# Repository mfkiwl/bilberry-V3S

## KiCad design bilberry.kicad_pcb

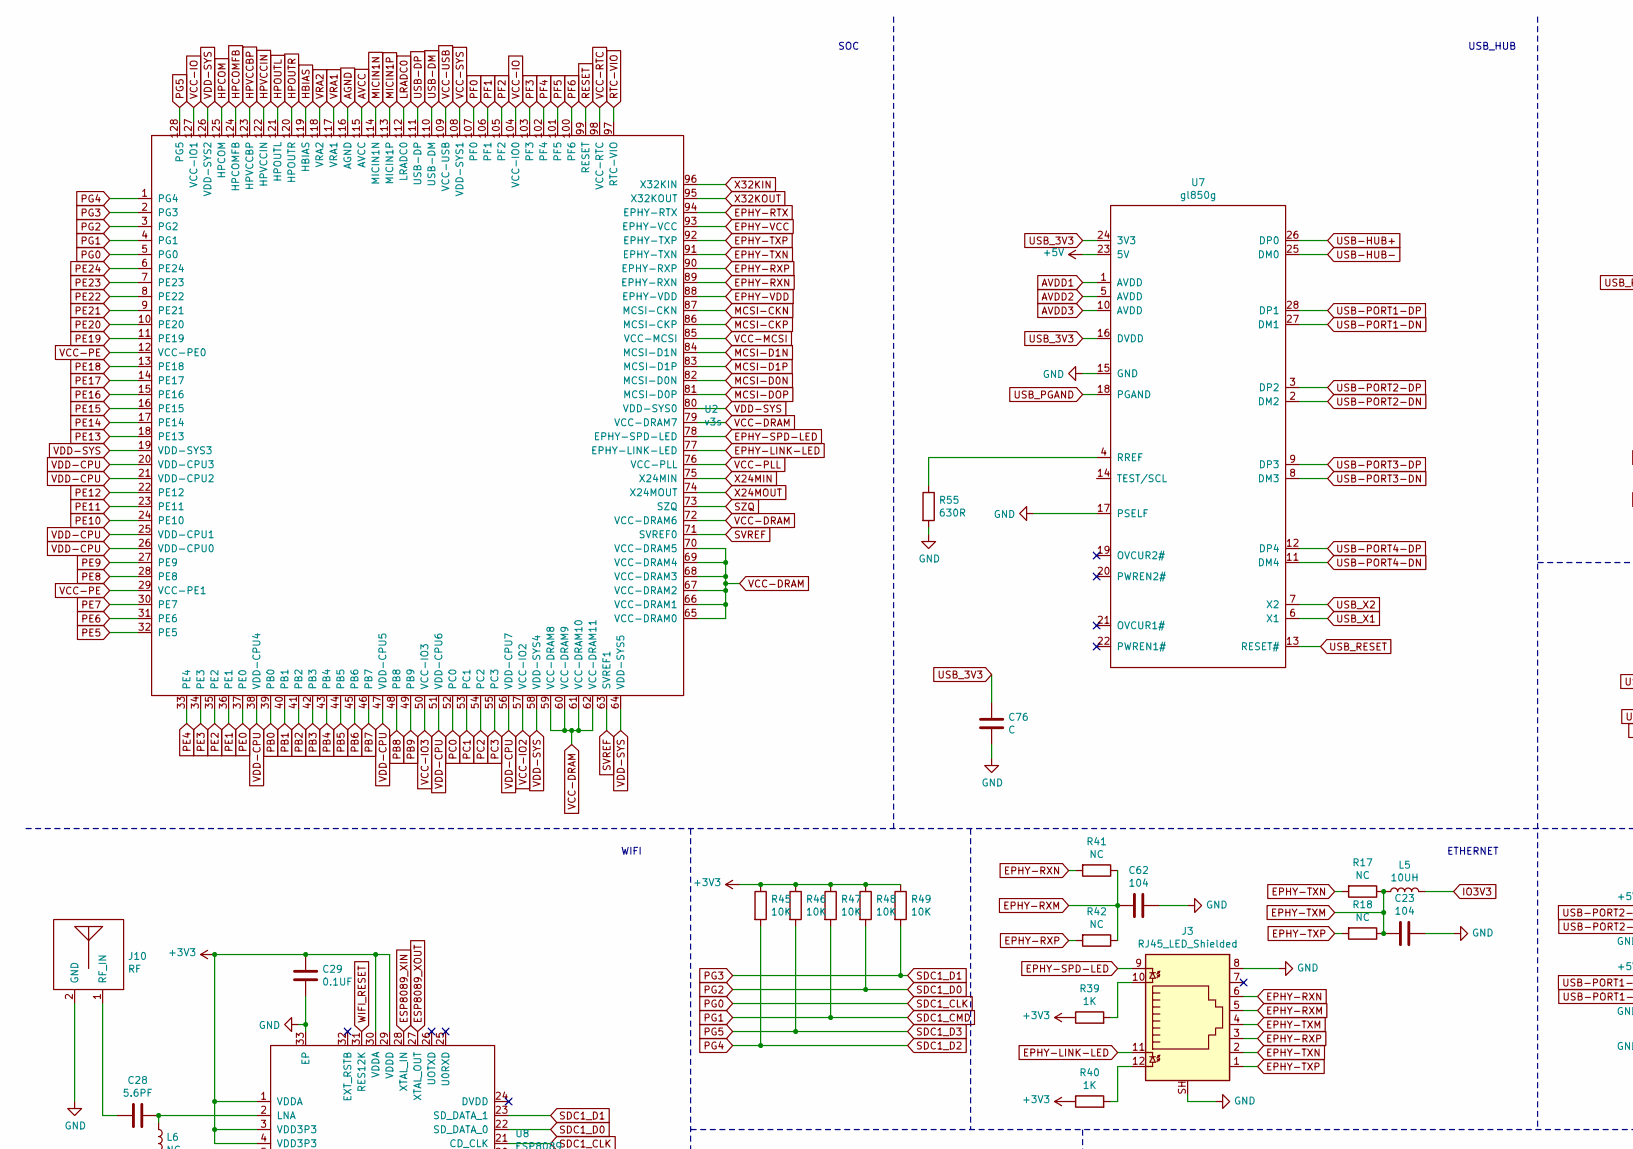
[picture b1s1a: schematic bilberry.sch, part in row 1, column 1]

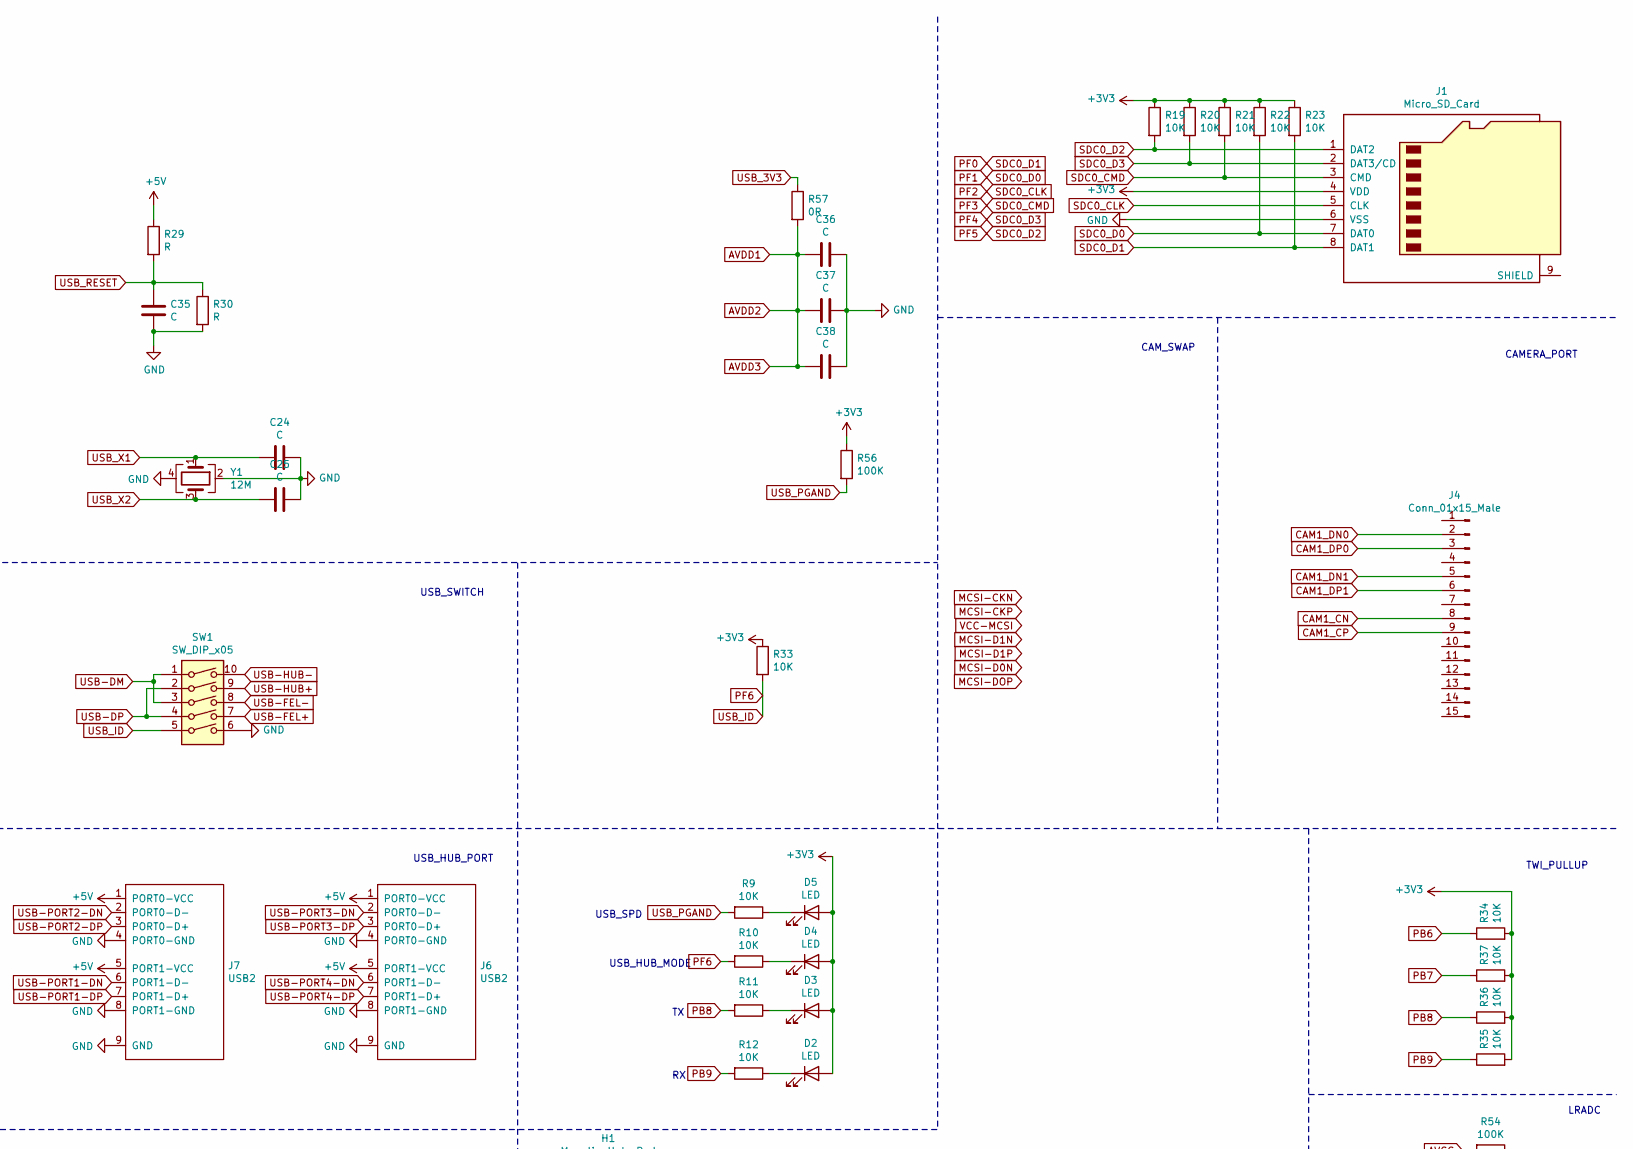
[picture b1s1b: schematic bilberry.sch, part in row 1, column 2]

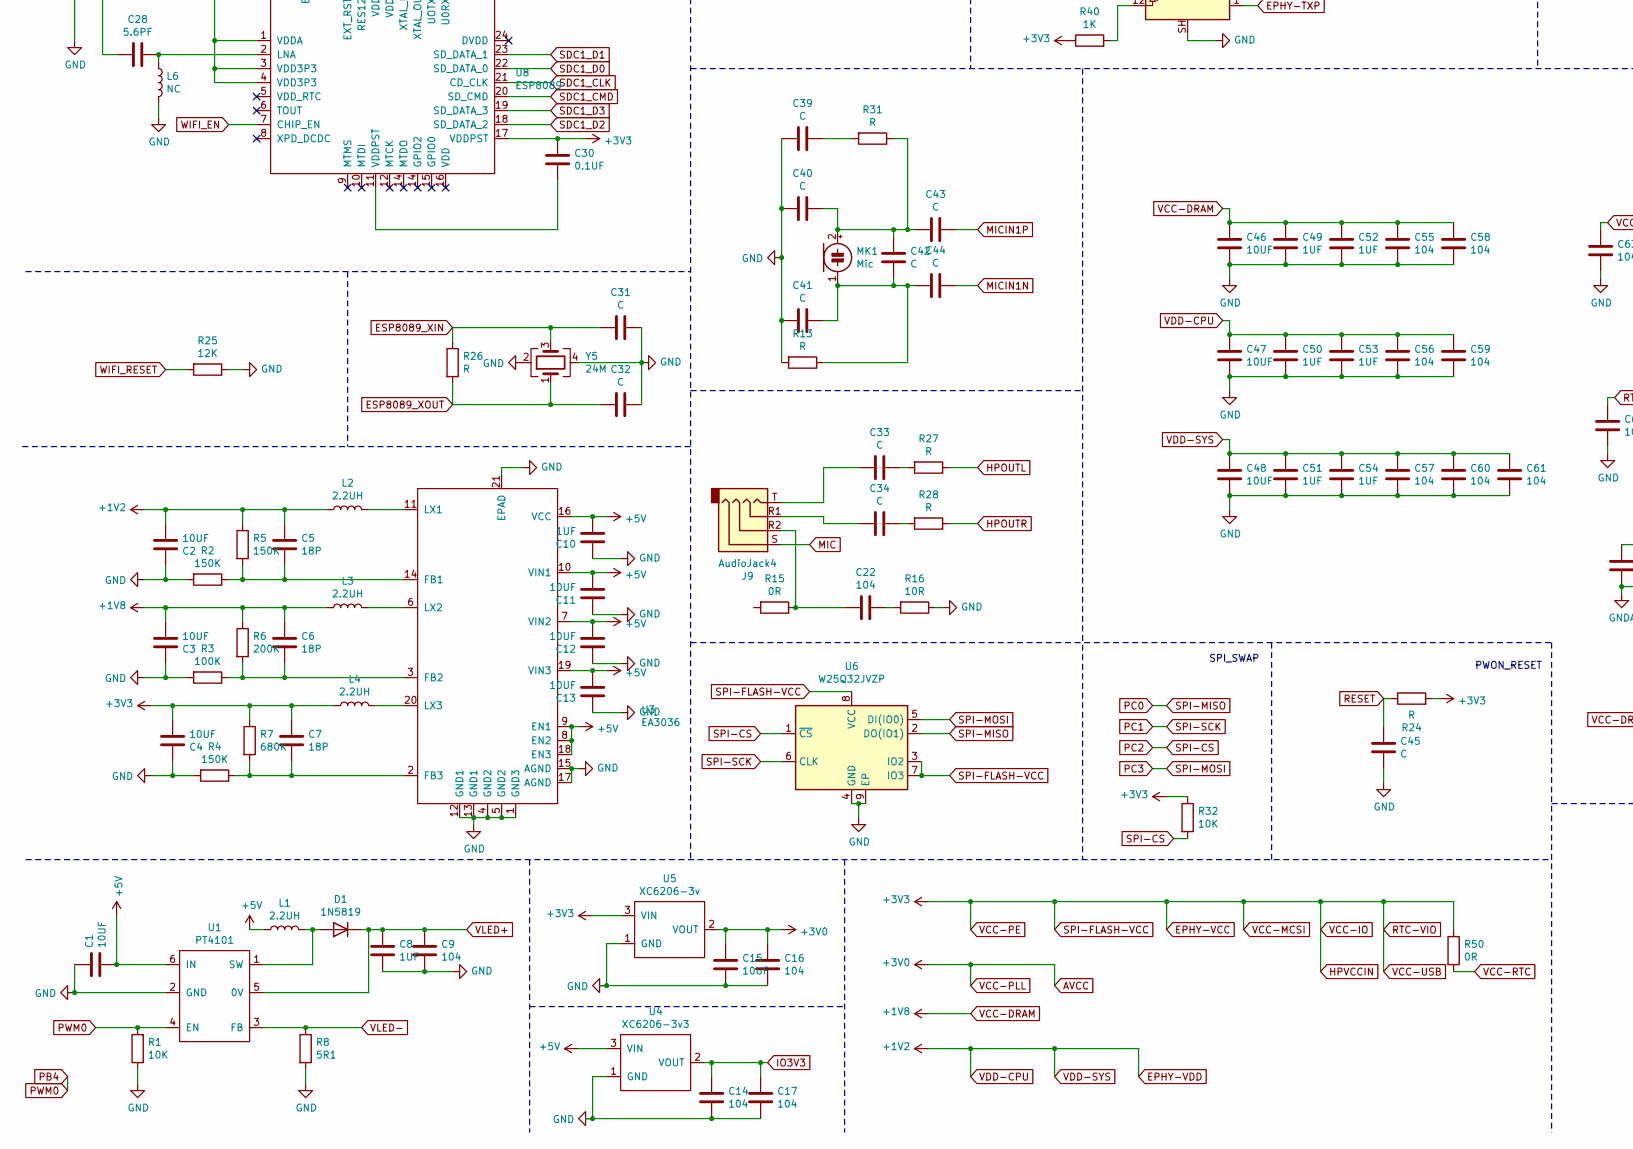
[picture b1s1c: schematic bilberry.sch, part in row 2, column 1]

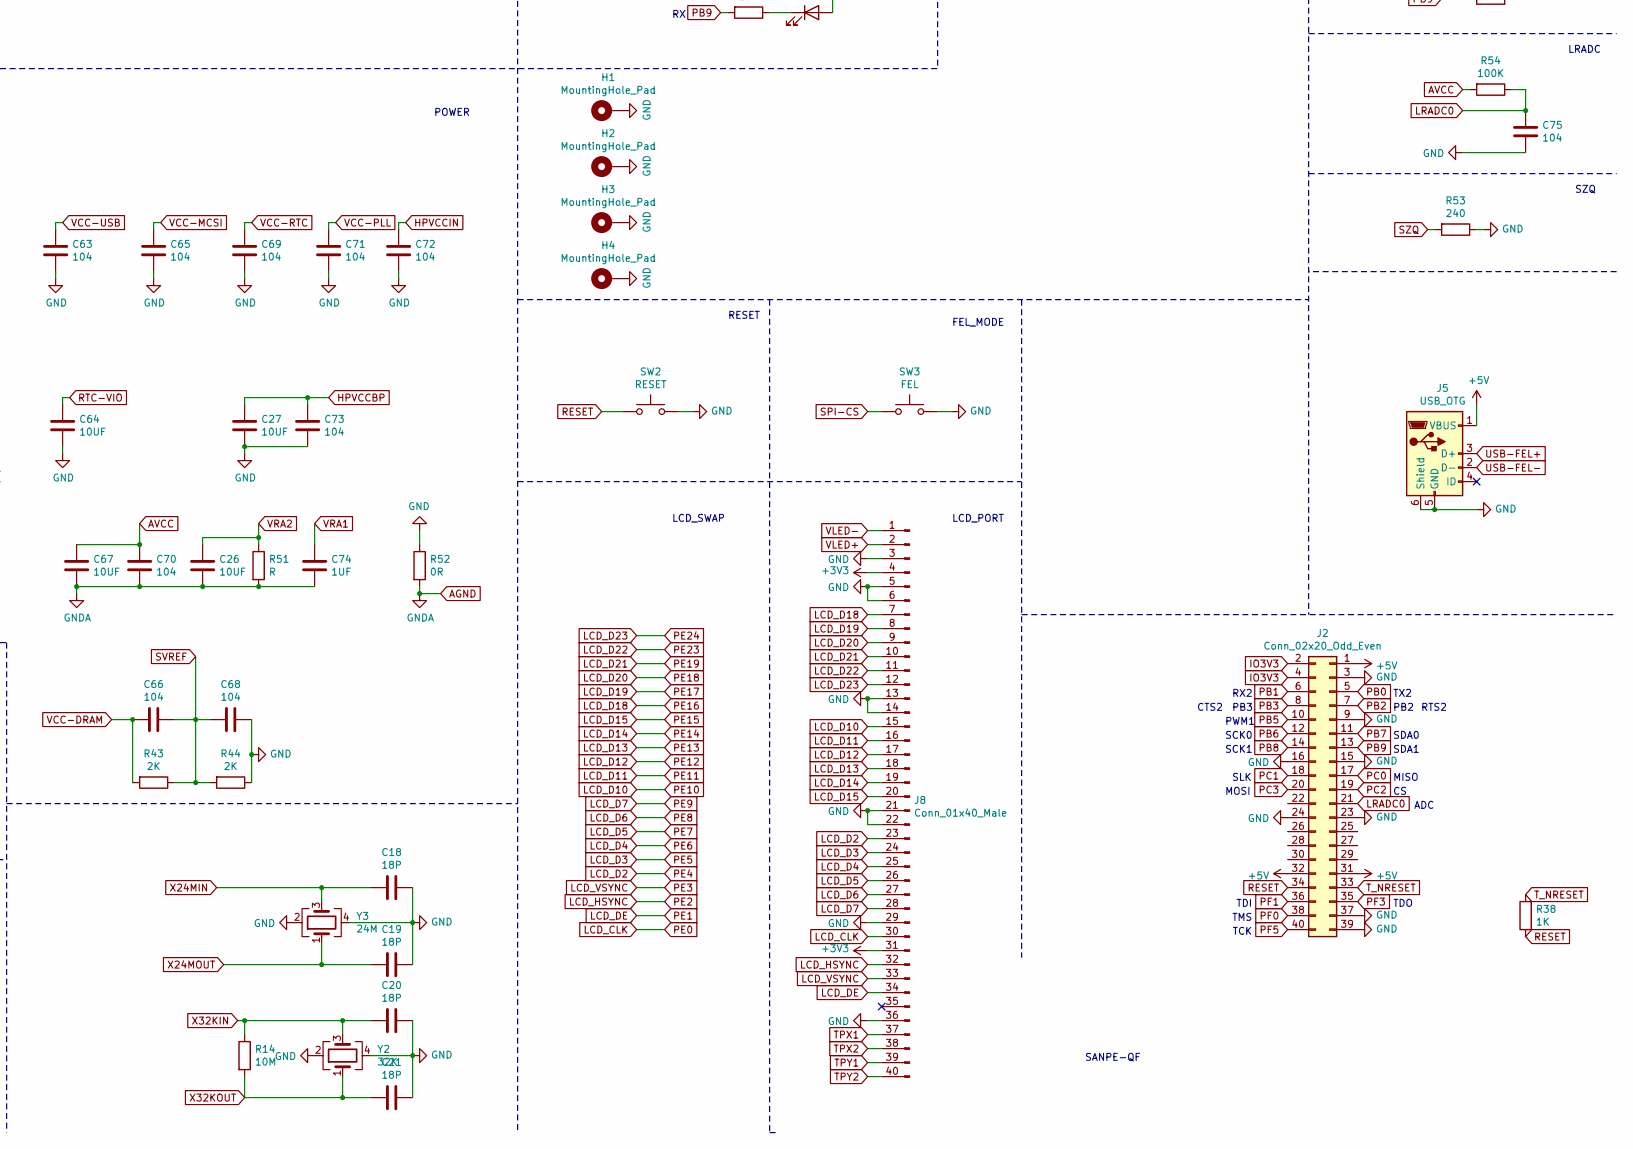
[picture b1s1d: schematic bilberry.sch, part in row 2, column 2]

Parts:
C1, C15, C26, C27, C46, C47, C48, C64, C67: 10UF; C_0603_1608Metric
C2, C3, C4, C11, C12, C13: 10UF; C_0805_2012Metric
C5, C6, C7, C18, C19, C20, C21: 18P; C_0603_1608Metric
C8, C49, C50, C51, C52, C53, C54, C74: 1UF; C_0603_1608Metric
C9, C14, C16, C17, C22, C23, C55, C56, C57, C58, C59, C60, C61, C62, C63, C65, C66, C68, C69, C70, C71, C72, C73, C75: 104; C_0603_1608Metric
C10: 1UF; C_0805_2012Metric
C24, C25, C31, C32, C33, C34, C35, C36, C37, C38, C39, C40, C41, C42, C43, C44, C45, C76: C; C_0603_1608Metric
C28: 5.6PF; C_0603_1608Metric
C29, C30: 0.1UF; C_0603_1608Metric
D1: 1N5819; D_0603_1608Metric
D2, D3, D4, D5: LED; LED_0603_1608Metric
H1, H2, H3, H4: MountingHole_Pad; MountingHole_2.7mm_Pad_Via
J1: Micro_SD_Card; microSD_HC_Molex_104031-0811
J2: Conn_02x20_Odd_Even; PinHeader_2x20_P2.54mm_Vertical
J3: RJ45_LED_Shielded; RJ45_Hanrun_HR911105A
J4: Conn_01x15_Male; Molex_200528-0150_1x15-1MP_P1.00mm_Horizontal
J5: USB_OTG; USB_Micro-B_Molex-105017-0001
J6, J7: USB2
J8: Conn_01x40_Male; Hirose_FH12-40S-0.5SH_1x40-1MP_P0.50mm_Horizontal
J9: AudioJack4; Jack_3.5mm_PJ320D_Horizontal
J10: RF
L1, L2, L3, L4: 2.2UH; L_Coilcraft_XAL5030
L5: 10UH; L_0603_1608Metric
L6: NC; L_0603_1608Metric
MK1: Mic
R1, R9, R10, R11, R12, R19, R20, R21, R22, R23, R32, R33, R34, R35, R36, R37, R45, R46, R47, R48, R49: 10K; R_0603_1608Metric
R2, R4, R5: 150K; R_0603_1608Metric
R3, R54, R56: 100K; R_0603_1608Metric
R6: 200K; R_0603_1608Metric
R7: 680K; R_0603_1608Metric
R8: 5R1; R_0603_1608Metric
R13, R24, R26, R27, R28, R29, R30, R31, R51: R; R_0603_1608Metric
R14: 10M; R_0603_1608Metric
R15, R50, R52, R57: 0R; R_0603_1608Metric
R16: 10R; R_0603_1608Metric
R17, R18, R41, R42: NC; R_0603_1608Metric
R25: 12K; R_0603_1608Metric
R38, R39, R40: 1K; R_0603_1608Metric
R43, R44: 2K; R_0603_1608Metric
R53: 240; R_0603_1608Metric
R55: 630R; R_0603_1608Metric
SW1: SW_DIP_x05; SW_DIP_SPSTx05_Slide_9.78x14.88mm_W7.62mm_P2.54mm
SW2: RESET; SW_SPST_B3U-1000P
SW3: FEL; SW_SPST_B3U-1000P
U1: PT4101; TSOT-23-6
U2: v3s; TQFP-128_14x14mm_P0.4mm
U3: EA3036; QFN-20-1EP_5x5mm_P0.65mm_EP3.35x3.35mm_ThermalVias
U4: XC6206-3v3; Potentiometer_Bourns_3224W_Vertical
U5: XC6206-3v; Potentiometer_Bourns_3224W_Vertical
U6: W25Q32JVZP; WSON-8-1EP_6x5mm_P1.27mm_EP3.4x4.3mm
U7: gl850g; SSOP-28_5.3x10.2mm_P0.65mm
U8: ESP8089; QFN-32-1EP_5x5mm_P0.5mm_EP3.6x3.6mm_ThermalVias
Y1: 12M; Crystal_SMD_3225-4Pin_3.2x2.5mm
Y2: 32K; Crystal_SMD_3225-4Pin_3.2x2.5mm
Y3, Y5: 24M; Crystal_SMD_3225-4Pin_3.2x2.5mm

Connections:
+5V: C1.2, C10.2, C11.2, C12.2, C13.2, J2.1, J2.31, J2.32, J5.1 (VBUS), J6.1 (PORT0-VCC), J6.5 (PORT1-VCC), J7.1 (PORT0-VCC), J7.5 (PORT1-VCC), L1.1, R29.1, U1.6 (IN), U3.7 (VIN2), U3.8 (EN2), U3.9 (EN1), U3.10 (VIN1), U3.16 (VCC), U3.18 (EN3), U3.19 (VIN3), U4.3 (VIN), U7.23 (5V)
AGND: C26.2, C67.2, C70.2, C74.2, R51.2, R52.2, U2.116 (AGND)
AVCC: C15.1, C16.1, C67.1, C70.1, C71.1, R54.2, U2.76 (VCC-PLL), U2.115 (AVCC), U5.2 (VOUT)
AVDD1: C36.2, C37.2, C38.2, R57.2, U7.1 (AVDD), U7.5 (AVDD), U7.10 (AVDD)
CAM1_CN: J4.8
CAM1_CP: J4.9
CAM1_DN0: J4.2
CAM1_DN1: J4.5
CAM1_DP0: J4.3
CAM1_DP1: J4.6
EPHY-LINK-LED: J3.11, U2.77 (EPHY-LINK-LED)
EPHY-RTX: U2.94 (EPHY-RTX)
EPHY-RXM: C62.2, J3.5, R41.1, R42.1
EPHY-RXN: J3.6, R41.2, U2.89 (EPHY-RXN)
EPHY-RXP: J3.3, R42.2, U2.90 (EPHY-RXP)
EPHY-SPD-LED: J3.9, U2.78 (EPHY-SPD-LED)
EPHY-TXM: C23.2, J3.4, L5.1, R17.1, R18.1
EPHY-TXN: J3.2, R17.2, U2.91 (EPHY-TXN)
EPHY-TXP: J3.1, R18.2, U2.92 (EPHY-TXP)
EPHY-VCC: C4.2, C7.1, C29.1, C30.1, C63.1, C64.1, C65.1, C72.1, D2.2 (A), D3.2 (A), D4.2 (A), D5.2 (A), J1.4 (VDD), J8.4, J8.31, L4.1, R7.1, R19.1, R20.1, R21.1, R22.1, R23.1, R24.2, R32.1, R33.1, R34.2, R35.2, R36.2, R37.2, R39.1, R40.1, R45.1, R46.1, R47.1, R48.1, R49.1, R50.1, R56.1, U2.12 (VCC-PE0), U2.29 (VCC-PE1), U2.85 (VCC-MCSI), U2.93 (EPHY-VCC), U2.97 (RTC-VIO), U2.104 (VCC-IO0), U2.109 (VCC-USB), U2.122 (HPVCCIN), U2.127 (VCC-IO1), U5.3 (VIN), U6.3 (IO2), U6.7 (IO3), U6.8 (VCC), U8.1 (VDDA), U8.3 (VDD3P3), U8.4 (VDD3P3), U8.17 (VDDPST), U8.29 (VDDD), U8.30 (VDDA)
EPHY-VDD: C2.2, C5.1, C47.1, C48.1, C50.1, C51.1, C53.1, C54.1, C56.1, C57.1, C59.1, C60.1, C61.1, L2.1, R5.1, U2.19 (VDD-SYS3), U2.20 (VDD-CPU3), U2.21 (VDD-CPU2), U2.25 (VDD-CPU1), U2.26 (VDD-CPU0), U2.38 (VDD-CPU4), U2.47 (VDD-CPU5), U2.51 (VDD-CPU6), U2.56 (VDD-CPU7), U2.58 (VDD-SYS4), U2.64 (VDD-SYS5), U2.80 (VDD-SYS0), U2.88 (EPHY-VDD), U2.126 (VDD-SYS2)
ESP8089_XIN: C31.1, R26.1, U8.28 (XTAL_IN), Y5.3
ESP8089_XOUT: C32.1, R26.2, U8.27 (XTAL_OUT), Y5.1
GND: C1.1, C2.1, C3.1, C4.1, C8.2, C9.2, C10.1, C11.1, C12.1, C13.1, C14.2, C15.2, C16.2, C17.2, C18.2, C19.2, C20.2, C21.2, C23.1, C24.1, C25.1, C27.2, C29.2, C31.2, C32.2, C35.2, C36.1, C37.1, C38.1, C39.2, C40.2, C41.2, C45.2, C46.2, C47.2, C48.2, C49.2, C50.2, C51.2, C52.2, C53.2, C54.2, C55.2, C56.2, C57.2, C58.2, C59.2, C60.2, C61.2, C62.1, C63.2, C64.2, C65.2, C68.1, C69.2, C71.2, C72.2, C73.2, C75.2, C76.2, H1.1, H2.1, H3.1, H4.1, J1.6 (VSS), J2.3, J2.9, J2.15, J2.16, J2.23, J2.24, J2.37, J2.39, J3.8, J3.SH, J5.5 (GND), J5.6 (Shield), J6.4 (PORT0-GND), J6.8 (PORT1-GND), J6.9 (GND), J7.4 (PORT0-GND), J7.8 (PORT1-GND), J7.9 (GND), J8.3, J8.5, J8.6, J8.13, J8.14, J8.21, J8.22, J8.29, J8.36, J10.2 (GND), L6.2, R1.1, R2.2, R3.2, R4.2, R8.2, R13.2, R16.1, R25.1, R30.2, R44.1, R52.1, R53.1, R55.2, SW1.6, SW2.2, SW3.2, U1.2 (GND), U3.1 (GND3), U3.4 (GND2), U3.5 (GND2), U3.12 (GND1), U3.13 (GND1), U3.15 (AGND), U3.17 (AGND), U3.21 (EPAD), U4.1 (GND), U5.1 (GND), U6.4 (GND), U6.9 (EP), U7.15 (GND), U7.17 (PSELF), U8.33 (EP), Y1.2, Y1.4, Y2.2, Y2.4, Y3.2, Y3.4, Y5.2, Y5.4
HBIAS: U2.119 (HBIAS)
HPCOM: U2.125 (HPCOM)
HPCOMFB: U2.124 (HPCOMFB)
HPOUTL: R27.1, U2.121 (HPOUTL)
HPOUTR: R28.1, U2.120 (HPOUTR)
HPVCCBP: C27.1, C73.1, U2.123 (HPVCCBP)
IO3V3: C14.1, C17.1, J2.2, J2.4, L5.2, U4.2 (VOUT)
LCD_CLK: J8.30, U2.37 (PE0)
LCD_D2: J8.23, U2.33 (PE4)
LCD_D3: J8.24, U2.32 (PE5)
LCD_D4: J8.25, U2.31 (PE6)
LCD_D5: J8.26, U2.30 (PE7)
LCD_D6: J8.27, U2.28 (PE8)
LCD_D7: J8.28, U2.27 (PE9)
LCD_D10: J8.15, U2.24 (PE10)
LCD_D11: J8.16, U2.23 (PE11)
LCD_D12: J8.17, U2.22 (PE12)
LCD_D13: J8.18, U2.18 (PE13)
LCD_D14: J8.19, U2.17 (PE14)
LCD_D15: J8.20, U2.16 (PE15)
LCD_D18: J8.7, U2.15 (PE16)
LCD_D19: J8.8, U2.14 (PE17)
LCD_D20: J8.9, U2.13 (PE18)
LCD_D21: J8.10, U2.11 (PE19)
LCD_D22: J8.11, U2.7 (PE23)
LCD_D23: J8.12, U2.6 (PE24)
LCD_DE: J8.34, U2.36 (PE1)
LCD_HSYNC: J8.32, U2.35 (PE2)
LCD_VSYNC: J8.33, U2.34 (PE3)
LRADC0: C75.1, J2.21, R54.1, U2.112 (LRADC0)
MCSI-CKN: U2.87 (MCSI-CKN)
MCSI-CKP: U2.86 (MCSI-CKP)
MCSI-D0N: U2.82 (MCSI-D0N)
MCSI-D1N: U2.84 (MCSI-D1N)
MCSI-D1P: U2.83 (MCSI-D1P)
MCSI-DOP: U2.81 (MCSI-D0P)
MIC: J9.S
MICIN1N: C44.2, U2.114 (MICIN1N)
MICIN1P: C43.2, U2.113 (MICIN1P)
unnamed: C5.2, R2.1, R5.2, U3.14 (FB1)
unnamed: C6.2, R3.1, R6.2, U3.3 (FB2)
unnamed: C7.2, R4.1, R7.2, U3.2 (FB3)
unnamed: C22.1, R16.2
unnamed: C22.2, J9.R2, R15.1
unnamed: C28.1, L6.1, U8.2 (LNA)
unnamed: C28.2, J10.1 (RF_IN)
unnamed: C30.2, U8.11 (VDDPST)
unnamed: C33.1, J9.T
unnamed: C33.2, R27.2
unnamed: C34.1, J9.R1
unnamed: C34.2, R28.2
unnamed: C39.1, R31.2
unnamed: C40.1, C42.1, C43.1, MK1.2 (+), R31.1
unnamed: C41.1, C42.2, C44.1, MK1.1 (-), R13.1
unnamed: D1.2 (A), L1.2, U1.1 (SW)
unnamed: D2.1 (K), R12.1
unnamed: D3.1 (K), R11.1
unnamed: D4.1 (K), R10.1
unnamed: D5.1 (K), R9.1
unnamed: J3.10, R39.2
unnamed: J3.12, R40.2
unnamed: L2.2, U3.11 (LX1)
unnamed: L3.2, U3.6 (LX2)
unnamed: L4.2, U3.20 (LX3)
unnamed: R55.1, U7.4 (RREF)
PB0: J2.5, U2.39 (PB0)
PB1: J2.6, U2.40 (PB1)
PB2: J2.7, U2.41 (PB2)
PB3: J2.8, U2.42 (PB3)
PB4: R1.2, U1.4 (EN), U2.43 (PB4)
PB5: J2.10, U2.44 (PB5)
PB6: J2.12, R34.1, U2.45 (PB6)
PB7: J2.11, R37.1, U2.46 (PB7)
PB8: J2.14, R11.2, R36.1, U2.48 (PB8)
PB9: J2.13, R12.2, R35.1, U2.49 (PB9)
PC0: J2.17, U2.52 (PC0), U6.2 (DO(IO1))
PC1: J2.18, U2.53 (PC1), U6.6 (CLK)
PC2: J2.19, R32.2, SW3.1, U2.54 (PC2), U6.1 (~CS)
PC3: J2.20, U2.55 (PC3), U6.5 (DI(IO0))
PE20: U2.10 (PE20)
PE21: U2.9 (PE21)
PE22: U2.8 (PE22)
PF6: R10.2, R33.2, SW1.5, U2.100 (PF6)
PG0: U2.5 (PG0), U8.21 (CD_CLK)
PG1: R47.2, U2.4 (PG1), U8.20 (SD_CMD)
PG2: R48.2, U2.3 (PG2), U8.22 (SD_DATA_0)
PG3: R49.2, U2.2 (PG3), U8.23 (SD_DATA_1)
PG4: R45.2, U2.1 (PG4), U8.18 (SD_DATA_2)
PG5: R46.2, U2.128 (PG5), U8.19 (SD_DATA_3)
RESET: C45.1, J2.34, R24.1, R38.1, SW2.1, U2.99 (RESET)
SVREF: C66.1, C68.2, R43.1, R44.2, U2.63 (SVREF1), U2.71 (SVREF0)
SZQ: R53.2, U2.73 (SZQ)
TPX1: J8.37
TPX2: J8.38
TPY1: J8.39
TPY2: J8.40
T_NRESET: J2.33, R38.2
USB-DM: SW1.1, SW1.3, U2.110 (USB-DM)
USB-DP: SW1.2, SW1.4, U2.111 (USB-DP)
USB-FEL+: J5.3 (D+), SW1.7
USB-FEL-: J5.2 (D-), SW1.8
USB-HUB+: SW1.9, U7.26 (DP0)
USB-HUB-: SW1.10, U7.25 (DM0)
USB-PORT1-DN: J7.6 (PORT1-D-), U7.27 (DM1)
USB-PORT1-DP: J7.7 (PORT1-D+), U7.28 (DP1)
USB-PORT2-DN: J7.2 (PORT0-D-), U7.2 (DM2)
USB-PORT2-DP: J7.3 (PORT0-D+), U7.3 (DP2)
USB-PORT3-DN: J6.2 (PORT0-D-), U7.8 (DM3)
USB-PORT3-DP: J6.3 (PORT0-D+), U7.9 (DP3)
USB-PORT4-DN: J6.6 (PORT1-D-), U7.11 (DM4)
USB-PORT4-DP: J6.7 (PORT1-D+), U7.12 (DP4)
USB_3V3: C76.1, R57.1, U7.16 (DVDD), U7.24 (3V3)
USB_PGAND: R9.2, R56.2, U7.18 (PGAND)
USB_RESET: C35.1, R29.2, R30.1, U7.13 (RESET#)
USB_X1: C24.2, U7.6 (X1), Y1.1
USB_X2: C25.2, U7.7 (X2), Y1.3
VCC-DRAM: C3.2, C6.1, C46.1, C49.1, C52.1, C55.1, C58.1, C66.2, L3.1, R6.1, R43.2, U2.59 (VCC-DRAM8), U2.60 (VCC-DRAM9), U2.61 (VCC-DRAM10), U2.62 (VCC-DRAM11), U2.65 (VCC-DRAM0), U2.66 (VCC-DRAM1), U2.67 (VCC-DRAM2), U2.68 (VCC-DRAM3), U2.69 (VCC-DRAM4), U2.70 (VCC-DRAM5), U2.72 (VCC-DRAM6), U2.79 (VCC-DRAM7)
VCC-IO2: U2.57 (VCC-IO2)
VCC-IO3: U2.50 (VCC-IO3)
VCC-RTC: C69.1, R50.2, U2.98 (VCC-RTC)
VCC-SYS: U2.108 (VDD-SYS1)
VLED+: C8.1, C9.1, D1.1 (K), J8.2, U1.5 (0V)
VLED-: J8.1, R8.1, U1.3 (FB)
VRA1: C74.1, U2.117 (VRA1)
VRA2: C26.1, R51.1, U2.118 (VRA2)
WIFI_EN: U8.7 (CHIP_EN)
WIFI_RESET: R25.2, U8.31 (RES12K)
X24MIN: C18.1, U2.75 (X24MIN), Y3.3
X24MOUT: C19.1, U2.74 (X24MOUT), Y3.1
X32KIN: C20.1, R14.1, U2.96 (X32KIN), Y2.3
X32KOUT: C21.1, R14.2, U2.95 (X32KOUT), Y2.1

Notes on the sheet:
SANPE-QF
TX2
RX2
PB2
PB3
PWM1
SCK0
SDA0
SCK1
SDA1
MISO
SLK
MOSI
ADC
TDI
TMS
TCK
TDO
TWI_PULLUP
ETHERNET
WIFI
SOC
USB_HUB
POWER
LCD_PORT
USB_SWITCH
USB_HUB_PORT
LRADC
SZQ
FEL_MODE
RESET
PWON_RESET
SPI_SWAP
LCD_SWAP
CAMERA_PORT
CAM_SWAP
USB_HUB_MODE
USB_SPD
RTS2
CTS2

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
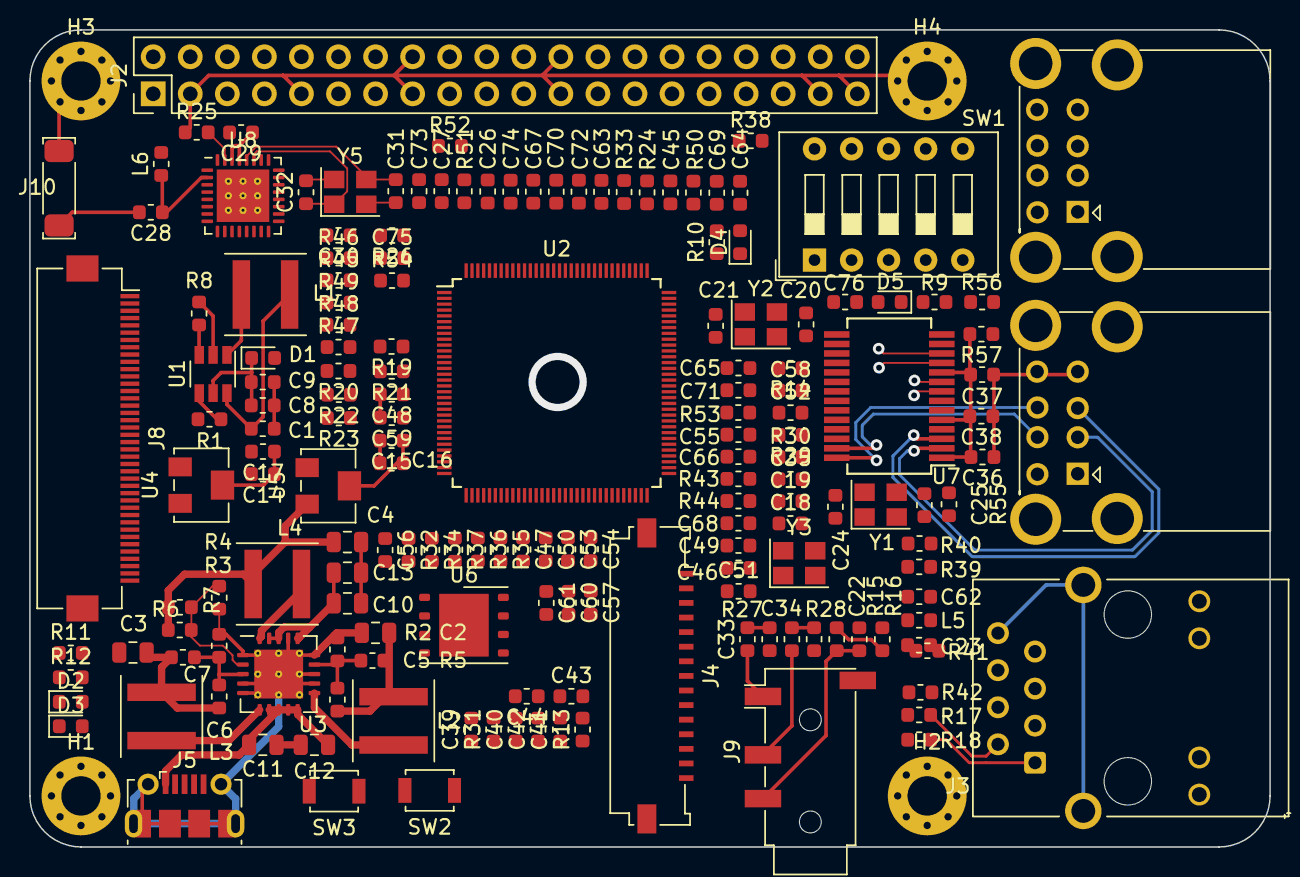
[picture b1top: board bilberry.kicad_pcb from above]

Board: 4 copper layers, 85.0 x 56.0 mm, 173 parts (1 on the bottom side), 136 nets.

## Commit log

2020-09-22 bilberry
